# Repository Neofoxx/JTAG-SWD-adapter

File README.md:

# JTAG-SWD-adapter
Universal JTAG/SWD/UART adapter based on FT2232H

#### PCB view

#### Finished product

### Pinout

## Description
This is a universal JTAG/SWD/UART/SPI/... adapter based around the FT2232H chip.
This initially started based off the KT-Link specifications, but has since evolved into the following set of features:

- USB Type-C connector
- 1.8V - 5V traget supply
- JTAG and SWD support on channel A, UART support on channel B.
- ESD protection of USB and of target
- Integrated power section, to power target from the adapter (5V/3.3V/2.5V/1.8V available)
- Similar pinout to the standard found on commercial JTAG/SWD adapters, with the addition of UART pins
- JTAG/SWD programming with simultaneous UART communication
- LEDs for USB power, Target power, SWD interface, Activity, and RX&TX of the UART

The design has been tested and confirmed working with OpenOCD.
Tested targets so far have been STM32F1 (SWD), STM32F3 (SWD), ESP32 (JTAG), and PIC32MX (JTAG)

## Component selection & BOM

Components were selected based on the desire to try them out, usually based on price/performance. FT2232H and its support circuitry should not be changed, but other things (series resistors, LEDs, DCDC chip) can be changed & exprimented with without issue.

## Setup (1/2) - EEPROM

After soldering the board together and verifying for no shorts, plug the debugger into your computer, and verify that it shows up. With no parameters in the EEPROM, it should show up as a generic FT2232H Dual UART device.

You can find the relevant files in the Setup folder.

### Windows

Use the provided "Neofoxx FT-Prog template.xml".
- Connect the device to your computer. Verify that VCP drivers for FT2232H are installed
- Open FT-Prog. Click on "Devices" -> "Scan and Parse"
- The device should now show up
- Right clock on your device, and select "Apply template". Choose the template in the first step.
- Afterwards, right-click on the device again, and select "Program". Confirm again that you want to progam the device.
- After programming, unplug & re-plug your device. Wait for driver installation.
- In FT-Prog, perform another "Scan and Parse".
- Confirm the device has the proper parameters.
- Success!

### Linux

- Use the provided "Neofoxx_ftdi_eeprom.conf". 
- (Feel free to change the serial number, but do not increase the number of characters)
- Install/build libftdi1 from https://www.intra2net.com/en/developer/libftdi/download.php
- (Link for reference, if you run into trouble: https://www.acmesystems.it/CM3-HOME_ft4232_setup )
- Flash the eeprom with the following command: `ftdi_eeprom --device i:0x0403:0x6010 --flash-eeprom Neofoxx_ftdi_eeprom.conf`
- Run the command again. Afterwards, unplug & re-plug the device.
- With dmesg or similar, you can check that the attached device now has the proper Manufacturer and Description string 
- Alternatively, in the examples folder, run the `eeprom` utility, and see what it outputs.

#### Known issues

- FT-Prog and ftdi_eeprom do not write 100% identical settings. The adapter will work nonetheless.
- If flashed with ftdi_eeprom, then checked in FT-Prog, the device will LOSE ITS PARAMETERS. In that case, upload them again in FT-Prog. If you don't check it in FT-Prog, it will work in Windows just fine. (Possible issue, that ftdi_eeprom doesn't write the eeprom type?)
- If you manage to mangle the parameters, and your VID/PID is suddenly 0000:0000, you can revive the device with a Windows box (virtualization won't work, unless you can pass a device with 0000:0000 to it).
- -> Connect the device to a Windows box, and force install the VCP drivers on the "Unknown device"
- -> This should then allow you to see the device in FT-Prog, and allow you to erase the eeprom and flash it with the proper parameters.

## Setup (2/2) - OpenOCD settings

- Copy the neofoxx.cfg file into your openocd scripts/interface/ftdi/ folder.

### Linux

- Done!

### Windows

- If you want to use the adapter with OpenOCD under Windows, you will have to change its driver from the FTDI one to a WinUSB one.
- Download Zadig from here: https://zadig.akeo.ie/
- Run the tool.
- If necessary, in the Options menu, select "List All Devices"
- Select "Neofoxx JTAG/SWD adapter (Interface 0)"
- Select WinUSB, then click Replace Driver.
- Done!
- Note, if you have multiple adapters connected at the same time and want to use them, you have to do this on all of them.
- If the adapter suddenly stops working under Windows, first check if the driver has changed. Windows have a nasty habit of changing things without telling you.

## Normal operation and things to look out for

- To use SWD with this board, you need to pass the proper flags to OpenOCD. Try something like this `openocd -f interface/ftdi/neofoxx.cfg -c "transport select swd" -f target/stm32f1x.cfg -c "adapter_khz 1000"`
- Because the board is compliant to the standard pinout, it will, when used in SWD mode, connect the TDO line to the RX of the UART channel, to be used as SWO.
- -> If this is undesired, the jumper on the board can be moved from "Auto" to "RX". This way, the UART RX pin will always be the RX pin, bypassing the switching of pins.
- The adapter includes a power section to power the target
- -> The maximum current draw is limited with a 1 ohm resistor, to protect the PC.
- -> When changing voltages, first turn the EN/1.8V pin to off, then set the voltage, then enable it again.
- -> When using 5V, disable the EN/1.8V switch first (the other two do not matter), then enable the 5V switch. Also in this case, if you make a mistake and short a high voltage onto the VTarget rail, your computer is at risk. There is some protection, but it's your computer. If you suspect this might happen, replace the 1 ohm resistor with an SMD fuse.
- The USB/Power LED shines when the USB cable is plugged in (5V is present)
- The VTarget LED shines when the voltage on VTarget is over 0.7V
- The SWD LED shines when the SWD interface is selected
- The Acivity light is SW driven from OpenOCD or others.

## Housing
The housing has been designed with latches, so it can be quickly opened and closed. 3D printing with PLA has given the best results so far.
Be warned, the housing was designed with minimal tolerances, so it might be a snug fit.

## Future improvements:

- Possibly split the two Vtarget pins into two separate pins - possibility of powering the target with say 5V, while communication works on 1.8V, etc.
- Instead of rounded corners, use inverted rounded corners, or no rounding at all. This would reduce waste during production of PCBs, since they could be panelized more easily (just V-cut, no mouse bites required)
- Fixup ftdi_eeprom & FT-Prog differences
- Update schematic to newer version of KiCad, and not use rescue symbols.
- Test the power section & enabling via the FTDI. As it is, that is UNTESTED

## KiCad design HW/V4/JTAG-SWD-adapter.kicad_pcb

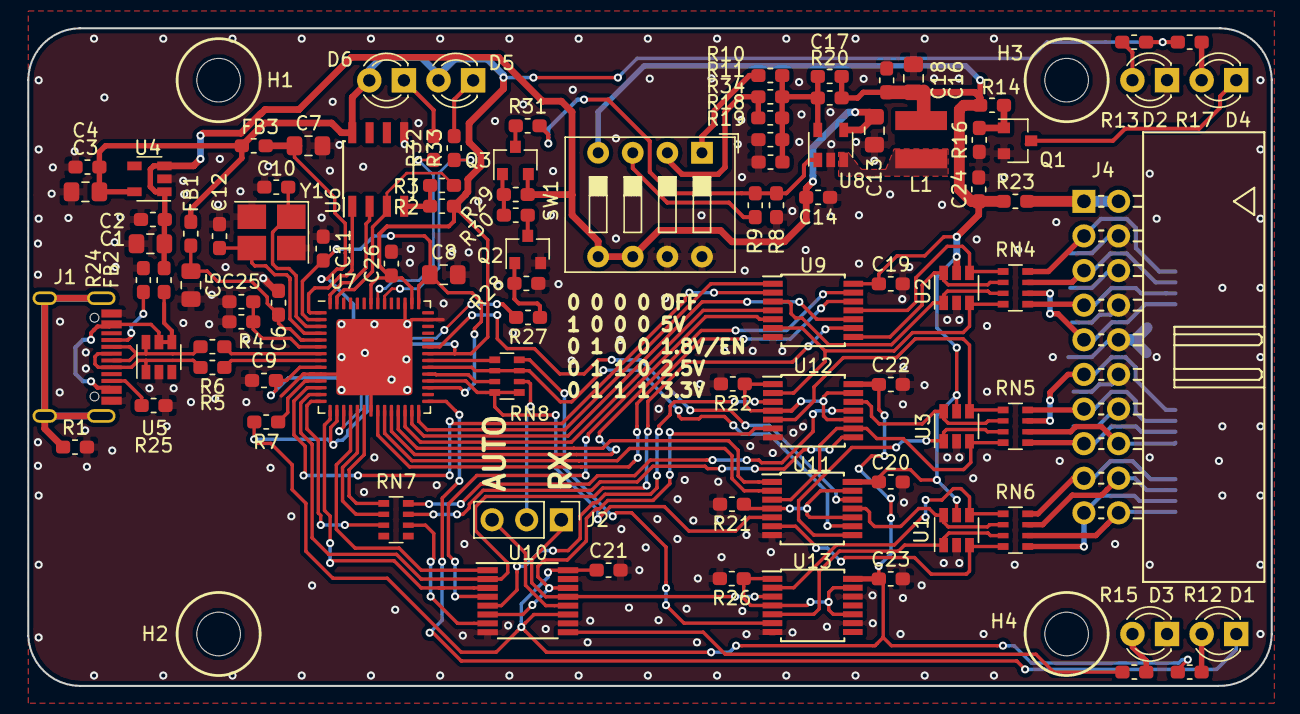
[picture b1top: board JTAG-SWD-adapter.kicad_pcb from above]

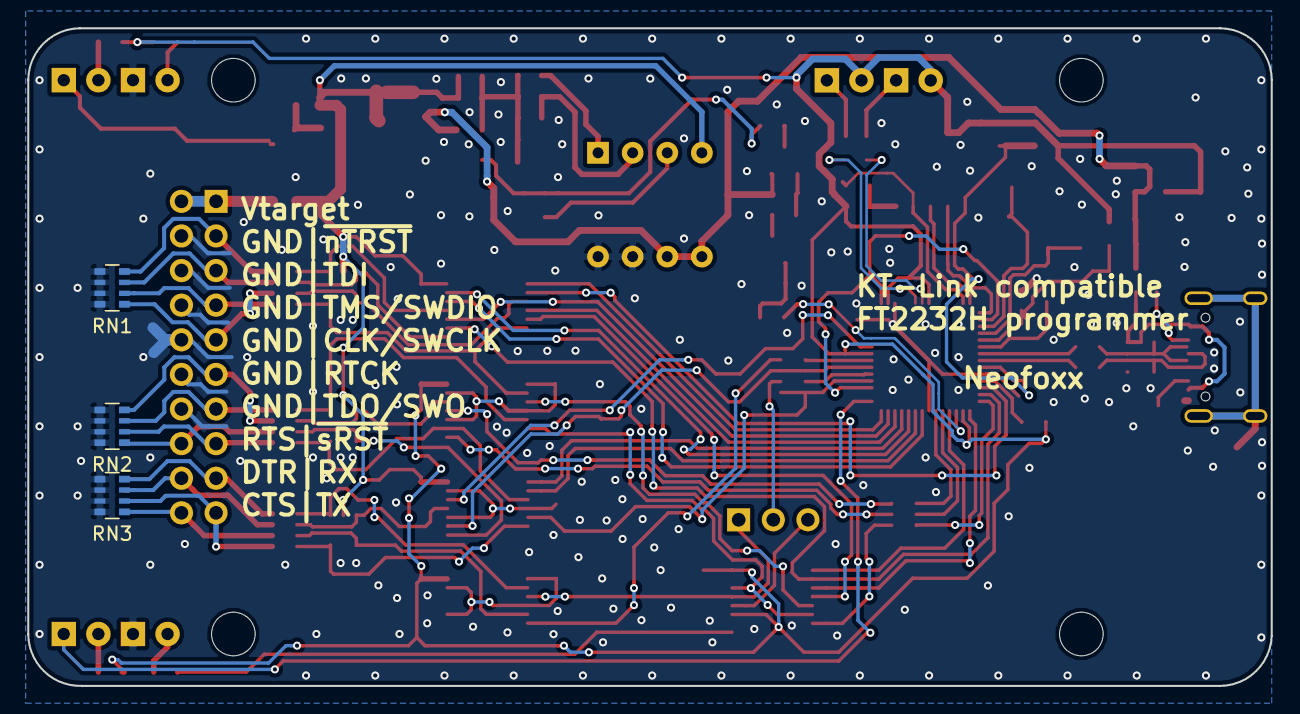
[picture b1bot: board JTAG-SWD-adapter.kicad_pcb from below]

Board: 2 copper layers, 91.2 x 48.3 mm, 103 parts (3 on the bottom side), 103 nets.

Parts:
C1, C3, C5, C7, C8: 4u7; C_0805_2012Metric_Pad1.15x1.40mm_HandSolder
C2, C4, C6, C9, C11, C14, C18, C19, C20, C21, C22, C23, C24, C26: 100nF; C_0603_1608Metric_Pad1.05x0.95mm_HandSolder
C10, C12: 27pF; C_0603_1608Metric_Pad1.05x0.95mm_HandSolder
C13, C16: 4.7uF; C_0805_2012Metric_Pad1.15x1.40mm_HandSolder
C17, C25: DNS; C_0603_1608Metric_Pad1.05x0.95mm_HandSolder
D1, D2, D3, D4, D5, D6: LED; LED_D3.0mm
FB1, FB3: 600R, 1A; L_0603_1608Metric_Pad1.05x0.95mm_HandSolder
FB2: 220R, 2.5A; L_0603_1608Metric_Pad1.05x0.95mm_HandSolder
H1, H2, H3, H4: MountingHole; MountingHole_3.2mm_M3
J1: USB_C_Receptacle_USB2.0; Jing USB C 2.0 16pin receptable
J2: Conn_01x03_Male; PinHeader_1x03_P2.54mm_Vertical
J4: CONN_02X10; Multicomp_MC9A22-2034_2x10_P2.54mm_Horizontal
L1: 1.5uH; SMNR4018_(1616FPS)
MARK1: LOGO; FOX_LOGO_MASK
Q1, Q2: BC847; SOT-23
Q3: BC857; SOT-23
R1: 0R; R_0603_1608Metric_Pad1.05x0.95mm_HandSolder
R2, R7, R27, R30: 10k; R_0603_1608Metric_Pad1.05x0.95mm_HandSolder
R3: 2k; R_0603_1608Metric_Pad1.05x0.95mm_HandSolder
R4: 12k; R_0603_1608Metric_Pad1.05x0.95mm_HandSolder
R5, R6: 10R; R_0603_1608Metric_Pad1.05x0.95mm_HandSolder
R8, R14, R16, R28, R29: 100k; R_0603_1608Metric_Pad1.05x0.95mm_HandSolder
R9, R12, R13, R15, R17, R21, R22, R26, R31, R32, R33: 1k; R_0603_1608Metric_Pad1.05x0.95mm_HandSolder
R10: 180k; R_0603_1608Metric_Pad1.05x0.95mm_HandSolder
R11: 470k; R_0603_1608Metric_Pad1.05x0.95mm_HandSolder
R18, R19, R20: 220k; R_0603_1608Metric_Pad1.05x0.95mm_HandSolder
R23: 1R; R_0603_1608Metric_Pad1.05x0.95mm_HandSolder
R24, R25: 5k1; R_0603_1608Metric_Pad1.05x0.95mm_HandSolder
R34: 330k; R_0603_1608Metric_Pad1.05x0.95mm_HandSolder
RN1, RN2, RN3: 4x470k; R_Array_Convex_4x0603
RN4, RN5, RN6, RN7, RN8: 4x220R; R_Array_Convex_4x0603
SW1: SW_DIP_x04; SW_DIP_SPSTx04_Slide_9.78x12.34mm_W7.62mm_P2.54mm
U1, U2, U3, U5: SRV05-4; SOT-23-6
U4: LN1134A332MR-G; SOT-23-5
U6: 93LCxxB; SOIC-8_3.9x4.9mm_P1.27mm
U7: FT2232H-56Q; QFN-56-1EP_8x8mm_P0.5mm_EP5.6x5.6mm
U8: BL8028; SOT-23-5
U9, U11, U12, U13: 74LVC125; TSSOP-14_4.4x5mm_P0.65mm
U10: 74LVC157A; TSSOP-16_4.4x5mm_P0.65mm
Y1: 12MHz; Crystal_SMD_3225-4Pin_3.2x2.5mm_HandSoldering

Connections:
+3V3: C3.1, C4.1, C21.1, C22.1, C23.1, C26.1, D5.2, D6.2, FB1.2, FB3.2, R2.1, R7.2, R12.2, R13.2, R17.1, U4.5, U6.8, U7.16, U7.36, U7.44, U7.50, U10.11, U10.16, U12.14, U13.14
+5V: C1.1, C2.1, C13.1, C14.1, FB2.1, Q3.2, R29.1, SW1.5, SW1.6, U4.1, U4.3, U8.4
/AC7/LED: D1.1, U7.29
/AD2/TDO: RN7.3, U7.14
/AD2/TDO_RES: RN7.6, U10.7
/AD6/SRST_SENS: RN7.2, U7.19
/AD6/SRST_SENS_RES: RN7.7, U12.8
/AD7/RTCK: RN7.1, U7.20
/AD7/RTCK_RES: RN7.8, U12.11
/BD0_TX_A: RN8.4, RN8.5, U7.32, U11.5
/BD1/RX: RN8.3, U7.33
/BD1/RX_RES: J2.2, RN8.6
/BD2_RTS_A: RN8.2, RN8.7, U7.34, U11.9
/BD3/CTS: RN8.1, U7.35
/BD3/CTS_RES: RN8.8, U13.6
/FTDI/AC0_TRST: U7.22, U9.12
/FTDI/AC1_SRST: U7.23, U11.2
/FTDI/AC2_TRST_OE: U7.24, U9.13
/FTDI/AC3_SRST_OE: U7.25, U11.1
/FTDI/AC4_TMS_OE: U7.26, U9.4
/FTDI/AC5_TDI_OE: U7.27, U9.10
/FTDI/AC6_TCK_OE: U7.28, U9.1
/FTDI/AD0_TCK: U7.12, U9.2
/FTDI/AD1_TDI: U7.13, U9.9, U10.2
/FTDI/AD3_TMS: U7.15, U10.3
/FTDI/AD5_MUX: U7.18, U10.1
/FTDI/BD4_DTR: U7.37, U11.12
/FTDI/EECLK: U6.2, U7.56
/FTDI/EECS: U6.1, U7.1
/FTDI/EEDATA: R3.1, U6.3, U7.55
/FTDI/EEDO: R2.2, R3.2, U6.4
/FTDI/VCORE: C8.1, C11.1, U7.2, U7.31, U7.43
/FTDI/VPHY: C5.1, C6.1, FB1.1, U7.5
/FTDI/VPLL: C7.1, C9.1, FB3.1, U7.9
/OutputBuffers/CMN_OE_IN1: R22.1, U12.1, U12.4, U12.10, U12.13
/OutputBuffers/CMN_OE_IN2: R26.1, U13.1, U13.4, U13.10, U13.13
/OutputBuffers/CMN_OE_OUT: R21.1, U11.4, U11.10, U11.13
/OutputBuffers/TDO_SENS: U10.6, U10.14, U12.6
/OutputBuffers/TMS_SENS: U10.5, U12.3
/OutputBuffers/TMS_UNBUF: U9.5, U10.4
/OutputBuffers/UART_RX_BUF: J2.1, U10.13, U13.3
/PWR_EN: R27.2, U7.17
/RTCK: J4.11, RN2.4, RN5.7
/RTCK_RES: RN5.2, U3.6, U12.12
/RXLED: R33.1, U7.48
/SWD_LED: R15.2, U10.9
/TCK/SWCLK: J4.9, RN1.1, RN4.6
/TCK/SWCLK_RES: RN4.3, U2.1, U9.3
/TDI: J4.5, RN1.3, RN4.7
/TDI_RES: RN4.2, U2.6, U9.8
/TDO/SWO: J4.13, RN2.3, RN5.8
/TDO/SWO_RES: RN5.1, U3.4, U12.5
/TMS/SWDIO: J4.7, RN1.2, RN4.5
/TMS/SWDIO_RES: RN4.4, U2.3, U9.6, U12.2
/TXLED: R32.1, U7.49
/UART_CTS: J4.20, RN3.1, RN6.6
/UART_CTS_RES: RN6.3, U1.1, U13.5
/UART_DTR: J4.18, RN3.3, RN6.7
/UART_DTR_RES: RN6.2, U1.6, U11.11
/UART_RTS: J4.16, RN2.1, RN5.6
/UART_RTS_RES: RN5.3, U3.1, U11.8
/UART_RX: J4.17, RN3.4, RN6.8
/UART_RX_RES: RN6.1, U1.4, U13.2
/UART_TX: J4.19, RN3.2, RN6.5
/UART_TX_RES: RN6.4, U1.3, U11.6
/~nSRST~/~RST~: J4.15, RN2.2, RN5.5
/~nSRST~/~RST~_RES: RN5.4, U3.3, U11.3, U12.9
/~nTRST~: J4.3, RN1.4, RN4.8
/~nTRST~_RES: RN4.1, U2.4, U9.11
GND: C1.2, C2.2, C3.2, C4.2, C5.2, C6.2, C7.2, C8.2, C9.2, C10.2, C11.2, C12.2, C13.2, C14.2, C16.2, C18.2, C19.2, C20.2, C21.2, C22.2, C23.2, C24.2, C25.2, C26.2, D2.1, D3.1, J1.A1, J4.4, J4.6, J4.8, J4.10, J4.12, J4.14, Q1.2, Q2.2, R1.2, R4.2, R8.1, R16.1, R18.1, R19.1, R21.2, R22.2, R24.2, R25.2, R26.2, R28.2, RN1.5, RN1.6, RN1.7, RN1.8, RN2.5, RN2.6, RN2.7, RN2.8, RN3.5, RN3.6, RN3.7, RN3.8, SW1.7, SW1.8, U1.2, U2.2, U3.2, U4.2, U5.2, U6.5, U7.10, U7.21, U7.41, U7.45, U7.57, U8.2, U9.7, U10.8, U10.10, U10.15, U11.7, U12.7, U13.7, U13.9, U13.12, Y1.2, Y1.4
unnamed: C10.1, U7.3, Y1.1
unnamed: C12.1, U7.4, Y1.3
unnamed: C17.2, R10.2, R11.2, R18.2, R19.2, R20.2, R34.2, U8.5
unnamed: C25.1, R4.1, U7.6
unnamed: D1.2, R12.1
unnamed: D2.2, R13.1
unnamed: D3.2, R15.1
unnamed: D4.1, Q1.3
unnamed: D4.2, R17.2
unnamed: D5.1, R33.2
unnamed: D6.1, R32.2
unnamed: FB2.2, J1.A4, U5.4, U5.5
unnamed: J1.A5, R24.1
unnamed: J1.A6, J1.B6, R5.2, U5.1
unnamed: J1.A7, J1.B7, R6.2, U5.6
unnamed: J1.B5, R25.1
unnamed: J1.S1, R1.1
unnamed: J2.3, U10.12
unnamed: J4.1, J4.2, R23.2
unnamed: L1.1, U8.3
unnamed: Q1.1, R14.1, R16.2
unnamed: Q2.1, R27.1, R28.1
unnamed: Q2.3, R30.2
unnamed: Q3.1, R29.2, R30.1
unnamed: Q3.3, R31.1
unnamed: R5.1, U7.8
unnamed: R6.1, U7.7
unnamed: R7.1, U7.11
unnamed: R9.2, SW1.3
unnamed: R10.1, SW1.1
unnamed: R11.1, R34.1, SW1.2
unnamed: R8.2, R9.1, R31.2, U8.1
VCC: C16.1, C17.1, C18.1, C19.1, C20.1, C24.1, L1.2, R14.2, R20.1, R23.1, SW1.4, U1.5, U2.5, U3.5, U9.14, U11.14

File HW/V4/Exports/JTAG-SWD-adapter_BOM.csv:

"Source:","/home/neofoxx/Projects/HW/JTAG-SWD-adapter/HW/V4/JTAG-SWD-adapter.sch"
"Date:","ned 11 avg 2019 10:19:47 CEST"
"Tool:","Eeschema 5.0.2-bee76a0~70~ubuntu18.04.1"
"Generator:","/usr/share/kicad/plugins/bom_csv_grouped_by_value_with_fp.py"
"Component Count:","103"
"Ref","Qnty","Value","Cmp name","Footprint","Description","Vendor"
"C1, C3, C5, C7, C8, ","5","4u7","C","Capacitor_SMD:C_0805_2012Metric_Pad1.15x1.40mm_HandSolder","Unpolarized capacitor",""
"C12, C10, ","2","27pF","C","Capacitor_SMD:C_0603_1608Metric_Pad1.05x0.95mm_HandSolder","Unpolarized capacitor",""
"C16, C13, ","2","4.7uF","C","Capacitor_SMD:C_0805_2012Metric_Pad1.15x1.40mm_HandSolder","Unpolarized capacitor",""
"C24, C2, C4, C6, C9, C11, C26, C18, C14, C20, C19, C23, C22, C21, ","14","100nF","C","Capacitor_SMD:C_0603_1608Metric_Pad1.05x0.95mm_HandSolder","",""
"C25, C17, ","2","DNS","C","Capacitor_SMD:C_0603_1608Metric_Pad1.05x0.95mm_HandSolder","Unpolarized capacitor",""
"D1, D2, D4, D3, D5, D6, ","6","LED","LED","LED_THT:LED_D3.0mm","",""
"FB1, FB3, ","2","600R, 1A","Ferrite_Bead_Small","Inductor_SMD:L_0603_1608Metric_Pad1.05x0.95mm_HandSolder","Ferrite bead, small symbol",""
"FB2, ","1","220R, 2.5A","Ferrite_Bead_Small","Inductor_SMD:L_0603_1608Metric_Pad1.05x0.95mm_HandSolder","Ferrite bead, small symbol",""
"H1, H2, H4, H3, ","4","MountingHole","MountingHole","MountingHole:MountingHole_3.2mm_M3","Mounting Hole without connection",""
"J1, ","1","USB_C_Receptacle_USB2.0","USB_C_Receptacle_USB2.0","KiCAD library:Jing USB C 2.0 16pin receptable","USB 2.0-only Type-C Receptacle connector",""
"J2, ","1","Conn_01x03_Male","Conn_01x03_Male","Connector_PinHeader_2.54mm:PinHeader_1x03_P2.54mm_Vertical","Generic connector, single row, 01x03, script generated (kicad-library-utils/schlib/autogen/connector/)",""
"J4, ","1","CONN_02X10","CONN_02X10","Connector_Multicomp:Multicomp_MC9A22-2034_2x10_P2.54mm_Horizontal","",""
"L1, ","1","1.5uH","L","KiCAD library:SMNR4018_(1616FPS)","Inductor",""
"MARK1, ","1","LOGO","LOGO","KiCAD library:FOX_LOGO_MASK","",""
"Q1, Q2, ","2","BC847","BC847","Package_TO_SOT_SMD:SOT-23","0.1A Ic, 45V Vce, NPN Transistor, SOT-23",""
"Q3, ","1","BC857","BC857","Package_TO_SOT_SMD:SOT-23","0.1A Ic, 45V Vce, PNP Transistor, SOT-23",""
"R1, ","1","0R","R","Resistor_SMD:R_0603_1608Metric_Pad1.05x0.95mm_HandSolder","Resistor",""
"R3, ","1","2k","R","Resistor_SMD:R_0603_1608Metric_Pad1.05x0.95mm_HandSolder","Resistor",""
"R4, ","1","12k","R","Resistor_SMD:R_0603_1608Metric_Pad1.05x0.95mm_HandSolder","Resistor",""
"R6, R5, ","2","10R","R","Resistor_SMD:R_0603_1608Metric_Pad1.05x0.95mm_HandSolder","Resistor",""
"R7, R2, R30, R27, ","4","10k","R","Resistor_SMD:R_0603_1608Metric_Pad1.05x0.95mm_HandSolder","Resistor",""
"R10, ","1","180k","R","Resistor_SMD:R_0603_1608Metric_Pad1.05x0.95mm_HandSolder","",""
"R11, ","1","470k","R","Resistor_SMD:R_0603_1608Metric_Pad1.05x0.95mm_HandSolder","",""
"R12, R13, R17, R15, R32, R33, R9, R31, R21, R22, R26, ","11","1k","R","Resistor_SMD:R_0603_1608Metric_Pad1.05x0.95mm_HandSolder","",""
"R14, R16, R8, R29, R28, ","5","100k","R","Resistor_SMD:R_0603_1608Metric_Pad1.05x0.95mm_HandSolder","Resistor",""
"R20, R18, R19, ","3","220k","R","Resistor_SMD:R_0603_1608Metric_Pad1.05x0.95mm_HandSolder","",""
"R23, ","1","1R","R","Resistor_SMD:R_0603_1608Metric_Pad1.05x0.95mm_HandSolder","Resistor",""
"R24, R25, ","2","5k1","R","Resistor_SMD:R_0603_1608Metric_Pad1.05x0.95mm_HandSolder","Resistor",""
"R34, ","1","330k","R","Resistor_SMD:R_0603_1608Metric_Pad1.05x0.95mm_HandSolder","",""
"RN1, RN2, RN3, ","3","4x470k","R_Pack04","Resistor_SMD:R_Array_Convex_4x0603","",""
"RN6, RN5, RN4, RN7, RN8, ","5","4x220R","R_Pack04","Resistor_SMD:R_Array_Convex_4x0603","",""
"SW1, ","1","SW_DIP_x04","SW_DIP_x04","Button_Switch_THT:SW_DIP_SPSTx04_Slide_9.78x12.34mm_W7.62mm_P2.54mm","4x DIP Switch, Single Pole Single Throw (SPST) switch, small symbol",""
"U2, U3, U1, U5, ","4","SRV05-4","SRV05-4","Package_TO_SOT_SMD:SOT-23-6","ESD Protection Diodes with Low Clamping Voltage, SOT-23-6",""
"U4, ","1","LN1134A332MR-G","AP2112K-3.3","Package_TO_SOT_SMD:SOT-23-5","600mA low dropout linear regulator, with enable pin, 3.8V-6V input voltage range, 3.3V fixed positive output, SOT-23-5 package",""
"U6, ","1","93LCxxB","93LCxxB","Package_SO:SOIC-8_3.9x4.9mm_P1.27mm","Serial EEPROM, 93 Series, 2.5V, DIP-8/SOIC-8",""
"U7, ","1","FT2232H-56Q","FT2232H-56Q","Package_DFN_QFN:QFN-56-1EP_8x8mm_P0.5mm_EP5.6x5.6mm","",""
"U8, ","1","BL8028","BL8028","Package_TO_SOT_SMD:SOT-23-5","",""
"U9, U11, U12, U13, ","4","74LVC125","74LVC125","Package_SO:TSSOP-14_4.4x5mm_P0.65mm","Quad buffer 3-State outputs",""
"U10, ","1","74LVC157A","74LS157-RESCUE-JTAG-SWD-adapter","Package_SO:TSSOP-16_4.4x5mm_P0.65mm","",""
"Y1, ","1","12MHz","Crystal_GND24","Crystal:Crystal_SMD_3225-4Pin_3.2x2.5mm_HandSoldering","Four pin crystal, GND on pins 2 and 4",""

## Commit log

2019-08-12 Addition of files for Rev4/V4 of the JTAG/SWD/UART adapter
2022-04-13 Fix a couple typos and add alt text to images
